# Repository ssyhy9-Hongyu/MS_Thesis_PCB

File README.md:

# MS_Thesis_PCB
PCB version control for current source inverter project

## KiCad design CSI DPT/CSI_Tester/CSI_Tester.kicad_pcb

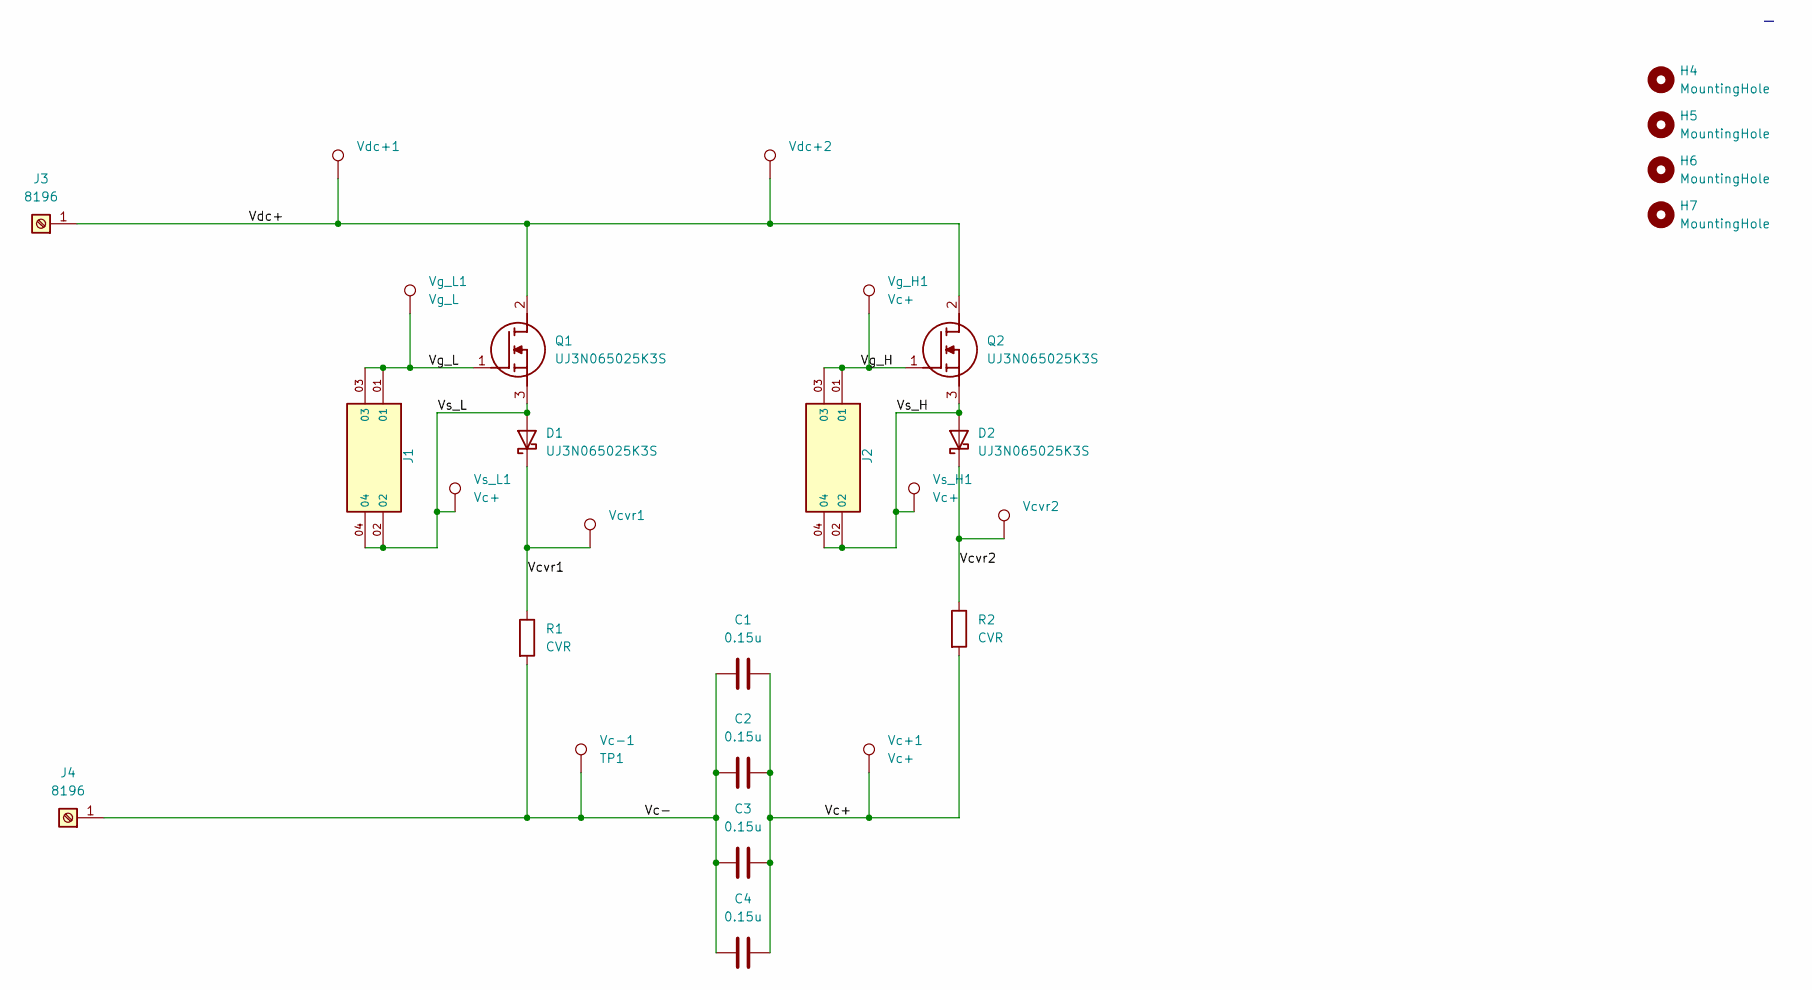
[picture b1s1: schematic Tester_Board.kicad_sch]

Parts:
C1, C2, C3, C4: 0.15u; C_Rect_L26.5mm_W10.5mm_P22.50mm_MKS4
D1, D2: UJ3N065025K3S; TO-247-2_Vertical
H4, H5, H6, H7: MountingHole; MountingHole_4.3mm_M4_DIN965
J1, J2: TSM-102-01-SM-DV; SAMTEC_TSM-102-01-SM-DV
J3, J4: 8196; CONN_8196_KEY
Q1, Q2: UJ3N065025K3S; TO-247-3_Vertical; Manufacturer_Part_Number UJ3N065025K3S
R1, R2: CVR; CVR_SSDN005
Vc+1: Vc+; TestPoint_Pad_D2.0mm
Vc-1: TP1; TestPoint_Pad_D2.0mm
Vcvr1, Vcvr2: TestPoint_Pad_D2.0mm
Vdc+1, Vdc+2: TestPoint_Pad_D2.0mm
Vg_H1: Vc+; TestPoint_Pad_D2.0mm
Vg_L1: Vg_L; TestPoint_Pad_D2.0mm
Vs_H1: Vc+; TestPoint_Pad_D2.0mm
Vs_L1: Vc+; TestPoint_Pad_D2.0mm

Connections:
/Tester_Board/Vc+: C1.2, C2.2, C3.2, C4.2, R2.2, Vc+1.1
/Tester_Board/Vc-: C1.1, C2.1, C3.1, C4.1, J4.1, J4.2, J4.3, J4.4, J4.5, J4.6, R1.2, Vc-1.1
/Tester_Board/Vcvr1: D1.1 (K), R1.1, Vcvr1.1
/Tester_Board/Vcvr2: D2.1 (K), R2.1, Vcvr2.1
/Tester_Board/Vdc+: J3.1, J3.2, J3.3, J3.4, J3.5, J3.6, Q1.2 (D), Q2.2 (D), Vdc+1.1, Vdc+2.1
/Tester_Board/Vg_H: J2.01, J2.03, Q2.1 (G), Vg_H1.1
/Tester_Board/Vg_L: J1.01, J1.03, Q1.1 (G), Vg_L1.1
/Tester_Board/Vs_H: D2.2 (A), J2.02, J2.04, Q2.3 (S), Vs_H1.1
/Tester_Board/Vs_L: D1.2 (A), J1.02, J1.04, Q1.3 (S), Vs_L1.1

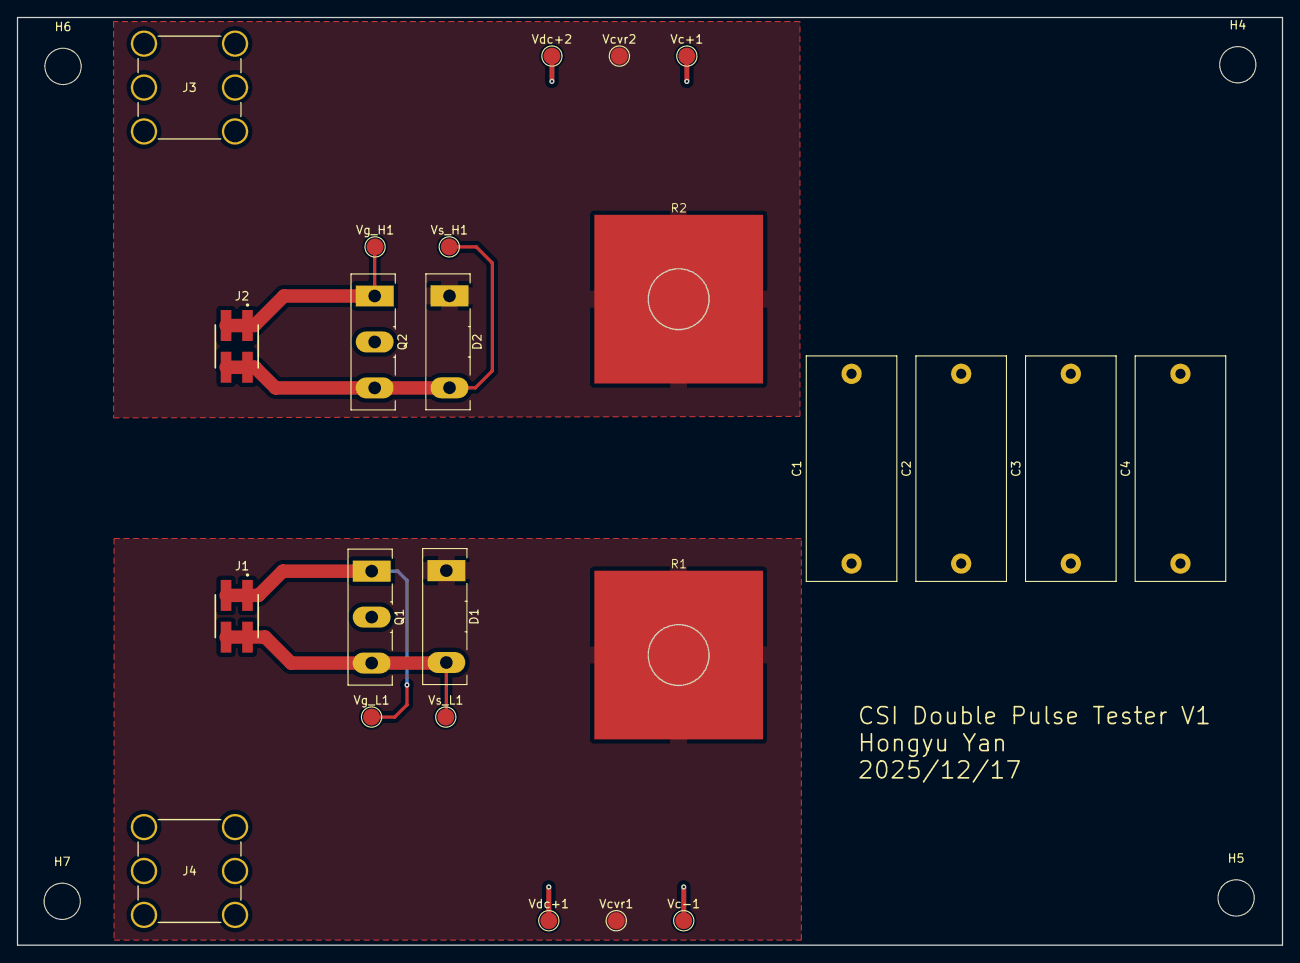
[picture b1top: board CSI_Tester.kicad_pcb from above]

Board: 4 copper layers, 150.0 x 110.0 mm, 28 parts (0 on the bottom side), 9 nets.

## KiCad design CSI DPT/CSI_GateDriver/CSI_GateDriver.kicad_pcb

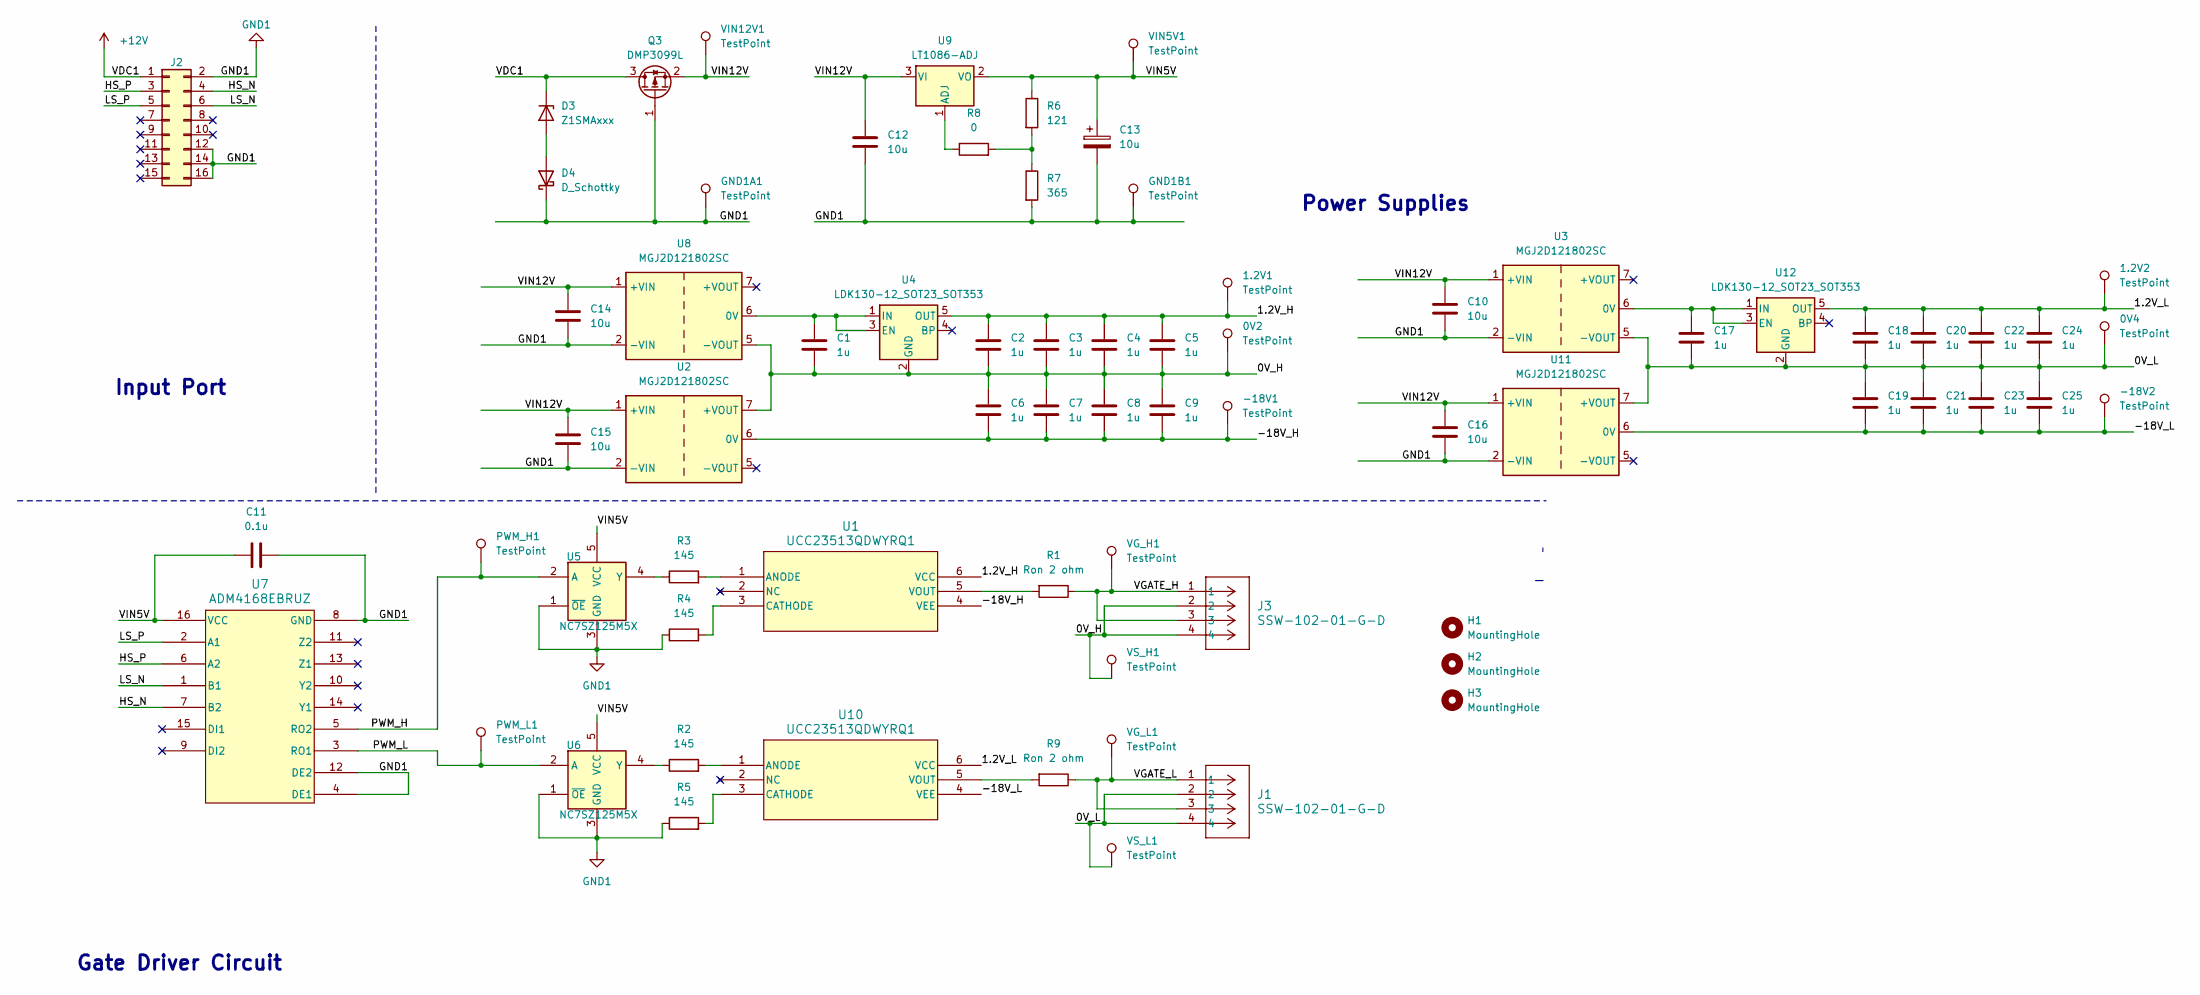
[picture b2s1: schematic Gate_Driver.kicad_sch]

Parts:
0V2, 0V4, 1.2V1, 1.2V2: TestPoint; TestPoint_Pad_D2.0mm
-18V1, -18V2: TestPoint; TestPoint_Pad_D2.0mm
C1, C2, C3, C4, C5, C6, C7, C8, C9, C17, C18, C19, C20, C21, C22, C23, C24, C25: 1u; C_1206_3216Metric
C10, C14, C15, C16: 10u; C_1206_3216Metric
C11: 0.1u; C_1206_3216Metric_Pad1.33x1.80mm_HandSolder
C12: 10u; C_1206_3216Metric_Pad1.33x1.80mm_HandSolder
C13: 10u; TAJB_AVX-M
D3: Z1SMAxxx; D_SMA_Handsoldering
D4: D_Schottky; D_PowerDI-123
GND1A1, GND1B1: TestPoint; TestPoint_Pad_D2.0mm
H1, H2, H3: MountingHole; MountingHole_4.3mm_M4_DIN965
J1, J3: SSW-102-01-G-D; CON4_2X2_TU_SSQ
J2: Conn_02x08_Odd_Even; IDC-Header_2x08_P2.54mm_Vertical
PWM_H1: TestPoint; TestPoint_Pad_D2.0mm
PWM_L1: TestPoint; TestPoint_Pad_D2.0mm
Q3: DMP3099L; SOT-23
R1, R9: Ron 2 ohm; R_1206_3216Metric_Pad1.30x1.75mm_HandSolder
R2, R3, R4, R5: 145; R_1206_3216Metric_Pad1.30x1.75mm_HandSolder
R6: 121; R_1206_3216Metric_Pad1.30x1.75mm_HandSolder
R7: 365; R_1206_3216Metric_Pad1.30x1.75mm_HandSolder
R8: 0; R_1206_3216Metric_Pad1.30x1.75mm_HandSolder
U1, U10: UCC23513QDWYRQ1; SOIC06_SO-6_7P5X4P68_TEX-M
U2, U3, U8, U11: MGJ2D121802SC; Converter_DCDC_Murata_MGJ2DxxxxxxSC_THT
U4, U12: LDK130-12_SOT23_SOT353; SOT-23-5_HandSoldering
U5, U6: NC7SZ125M5X; SOT-23-5_HandSoldering
U7: ADM4168EBRUZ; RU_16_ADI-M
U9: LT1086-ADJ; TO-263-3_TabPin2
VG_H1: TestPoint; TestPoint_Pad_D2.0mm
VG_L1: TestPoint; TestPoint_Pad_D2.0mm
VIN5V1, VIN12V1: TestPoint; TestPoint_Pad_D2.0mm
VS_H1: TestPoint; TestPoint_Pad_D2.0mm
VS_L1: TestPoint; TestPoint_Pad_D2.0mm

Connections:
+12V: D3.1 (K), J2.1, Q3.3 (D)
/Gate_Driver/0V_H: 0V2.1, C1.2, C2.2, C3.2, C4.2, C5.2, C6.1, C7.1, C8.1, C9.1, J3.2, J3.4, U2.7 (+VOUT), U4.2 (GND), U8.5 (-VOUT), VS_H1.1
/Gate_Driver/0V_L: 0V4.1, C17.2, C18.2, C19.1, C20.2, C21.1, C22.2, C23.1, C24.2, C25.1, J1.2, J1.4, U3.5 (-VOUT), U11.7 (+VOUT), U12.2 (GND), VS_L1.1
/Gate_Driver/1.2V_H: 1.2V1.1, C2.1, C3.1, C4.1, C5.1, U1.6 (VCC), U4.5 (OUT)
/Gate_Driver/1.2V_L: 1.2V2.1, C18.1, C20.1, C22.1, C24.1, U10.6 (VCC), U12.5 (OUT)
/Gate_Driver/-18V_H: -18V1.1, C6.2, C7.2, C8.2, C9.2, U1.4 (VEE), U2.6 (0V)
/Gate_Driver/-18V_L: -18V2.1, C19.2, C21.2, C23.2, C25.2, U10.4 (VEE), U11.6 (0V)
/Gate_Driver/HS_N: J2.4, U7.7 (B2)
/Gate_Driver/HS_P: J2.3, U7.6 (A2)
/Gate_Driver/LS_N: J2.6, U7.1 (B1)
/Gate_Driver/LS_P: J2.5, U7.2 (A1)
/Gate_Driver/PWM_H: PWM_H1.1, U5.2 (A), U7.5 (RO2)
/Gate_Driver/PWM_L: PWM_L1.1, U6.2 (A), U7.3 (RO1)
/Gate_Driver/VGATE_H: J3.1, J3.3, R1.1, VG_H1.1
/Gate_Driver/VGATE_L: J1.1, J1.3, R9.1, VG_L1.1
/Gate_Driver/VIN5V: C11.1, C13.1, R6.1, U5.5 (VCC), U6.5 (VCC), U7.16 (VCC), U9.2 (VO), VIN5V1.1
/Gate_Driver/VIN12V: C10.1, C12.1, C14.1, C15.1, C16.1, Q3.2 (S), U2.1 (+VIN), U3.1 (+VIN), U8.1 (+VIN), U9.3 (VI), U11.1 (+VIN), VIN12V1.1
GND1: C10.2, C11.2, C12.2, C13.2, C14.2, C15.2, C16.2, D4.1 (K), GND1A1.1, GND1B1.1, J2.2, J2.12, J2.14, J2.16, Q3.1 (G), R4.1, R5.1, R7.2, U2.2 (-VIN), U3.2 (-VIN), U5.1 (~OE), U5.3 (GND), U6.1 (~OE), U6.3 (GND), U7.4 (DE1), U7.8 (GND), U7.12 (DE2), U8.2 (-VIN), U11.2 (-VIN)
unnamed: D3.2 (A), D4.2 (A)
unnamed: R6.2, R7.1, R8.2
unnamed: R3.2, U1.1 (ANODE)
unnamed: R4.2, U1.3 (CATHODE)
unnamed: R1.2, U1.5 (VOUT)
unnamed: C1.1, U4.1 (IN), U4.3 (EN), U8.6 (0V)
unnamed: R3.1, U5.4 (Y)
unnamed: R2.1, U6.4 (Y)
unnamed: R8.1, U9.1 (ADJ)
unnamed: R2.2, U10.1 (ANODE)
unnamed: R5.2, U10.3 (CATHODE)
unnamed: R9.2, U10.5 (VOUT)
unnamed: C17.1, U3.6 (0V), U12.1 (IN), U12.3 (EN)

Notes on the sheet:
Gate Driver Circuit
Power Supplies
Input Port

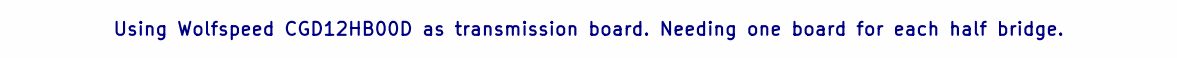
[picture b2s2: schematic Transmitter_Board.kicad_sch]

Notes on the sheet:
Using Wolfspeed CGD12HB00D as transmission board. Needing one board for each half bridge.

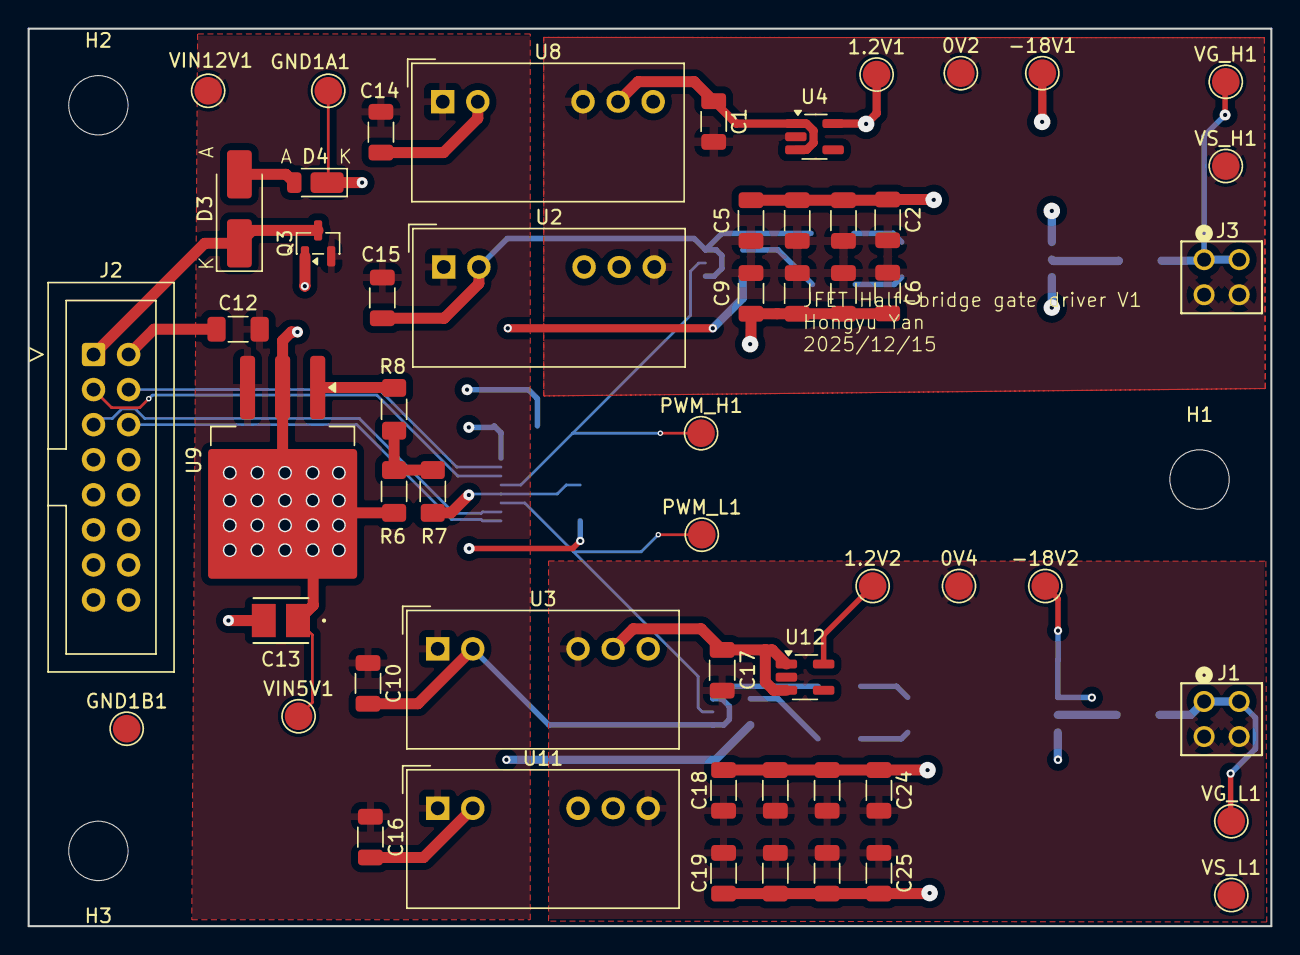
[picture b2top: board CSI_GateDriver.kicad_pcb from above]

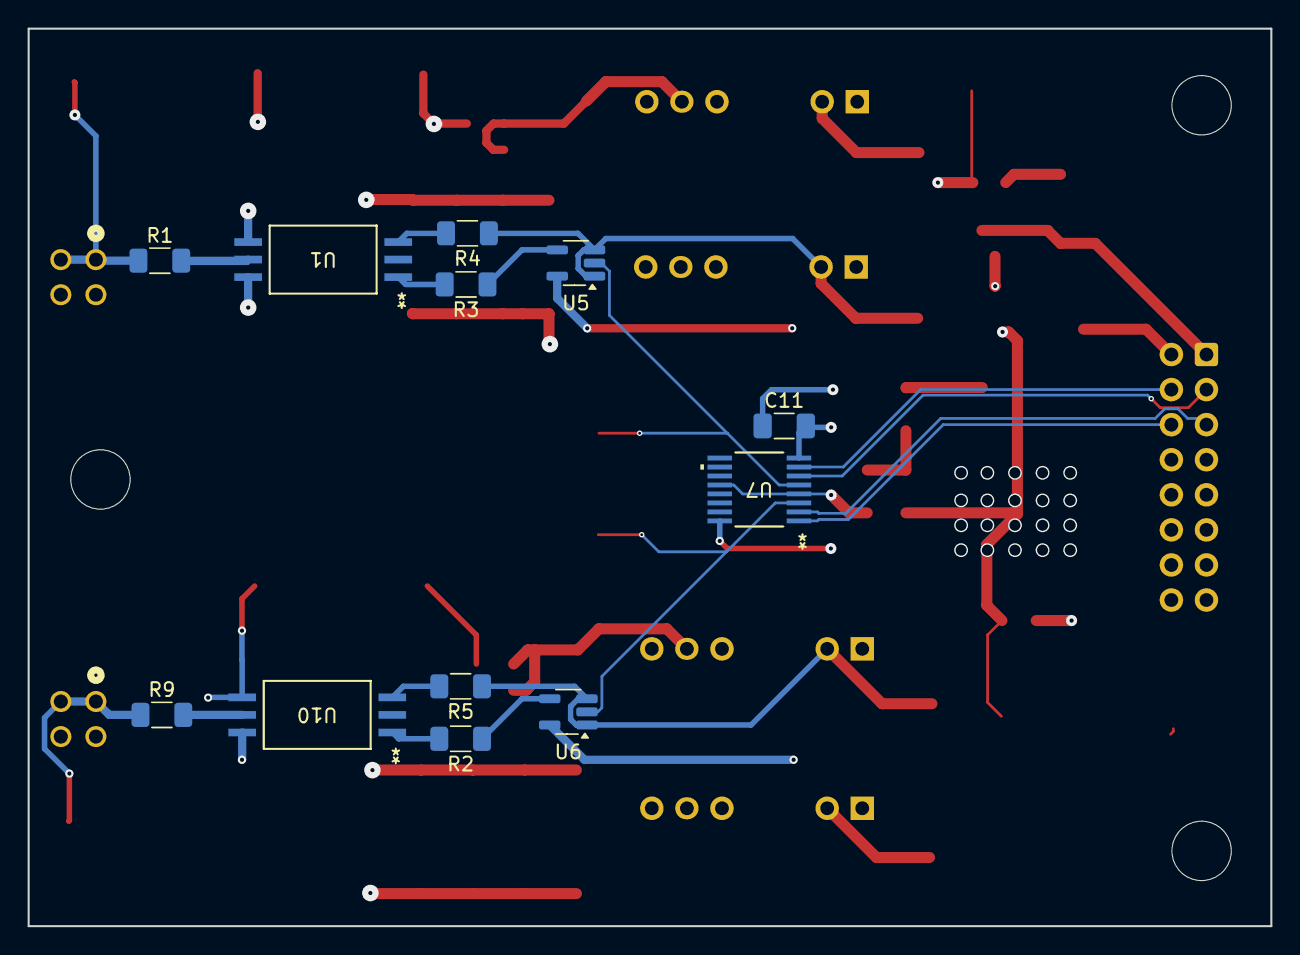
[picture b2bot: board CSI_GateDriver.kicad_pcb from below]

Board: 4 copper layers, 90.0 x 65.0 mm, 71 parts (12 on the bottom side), 31 nets.

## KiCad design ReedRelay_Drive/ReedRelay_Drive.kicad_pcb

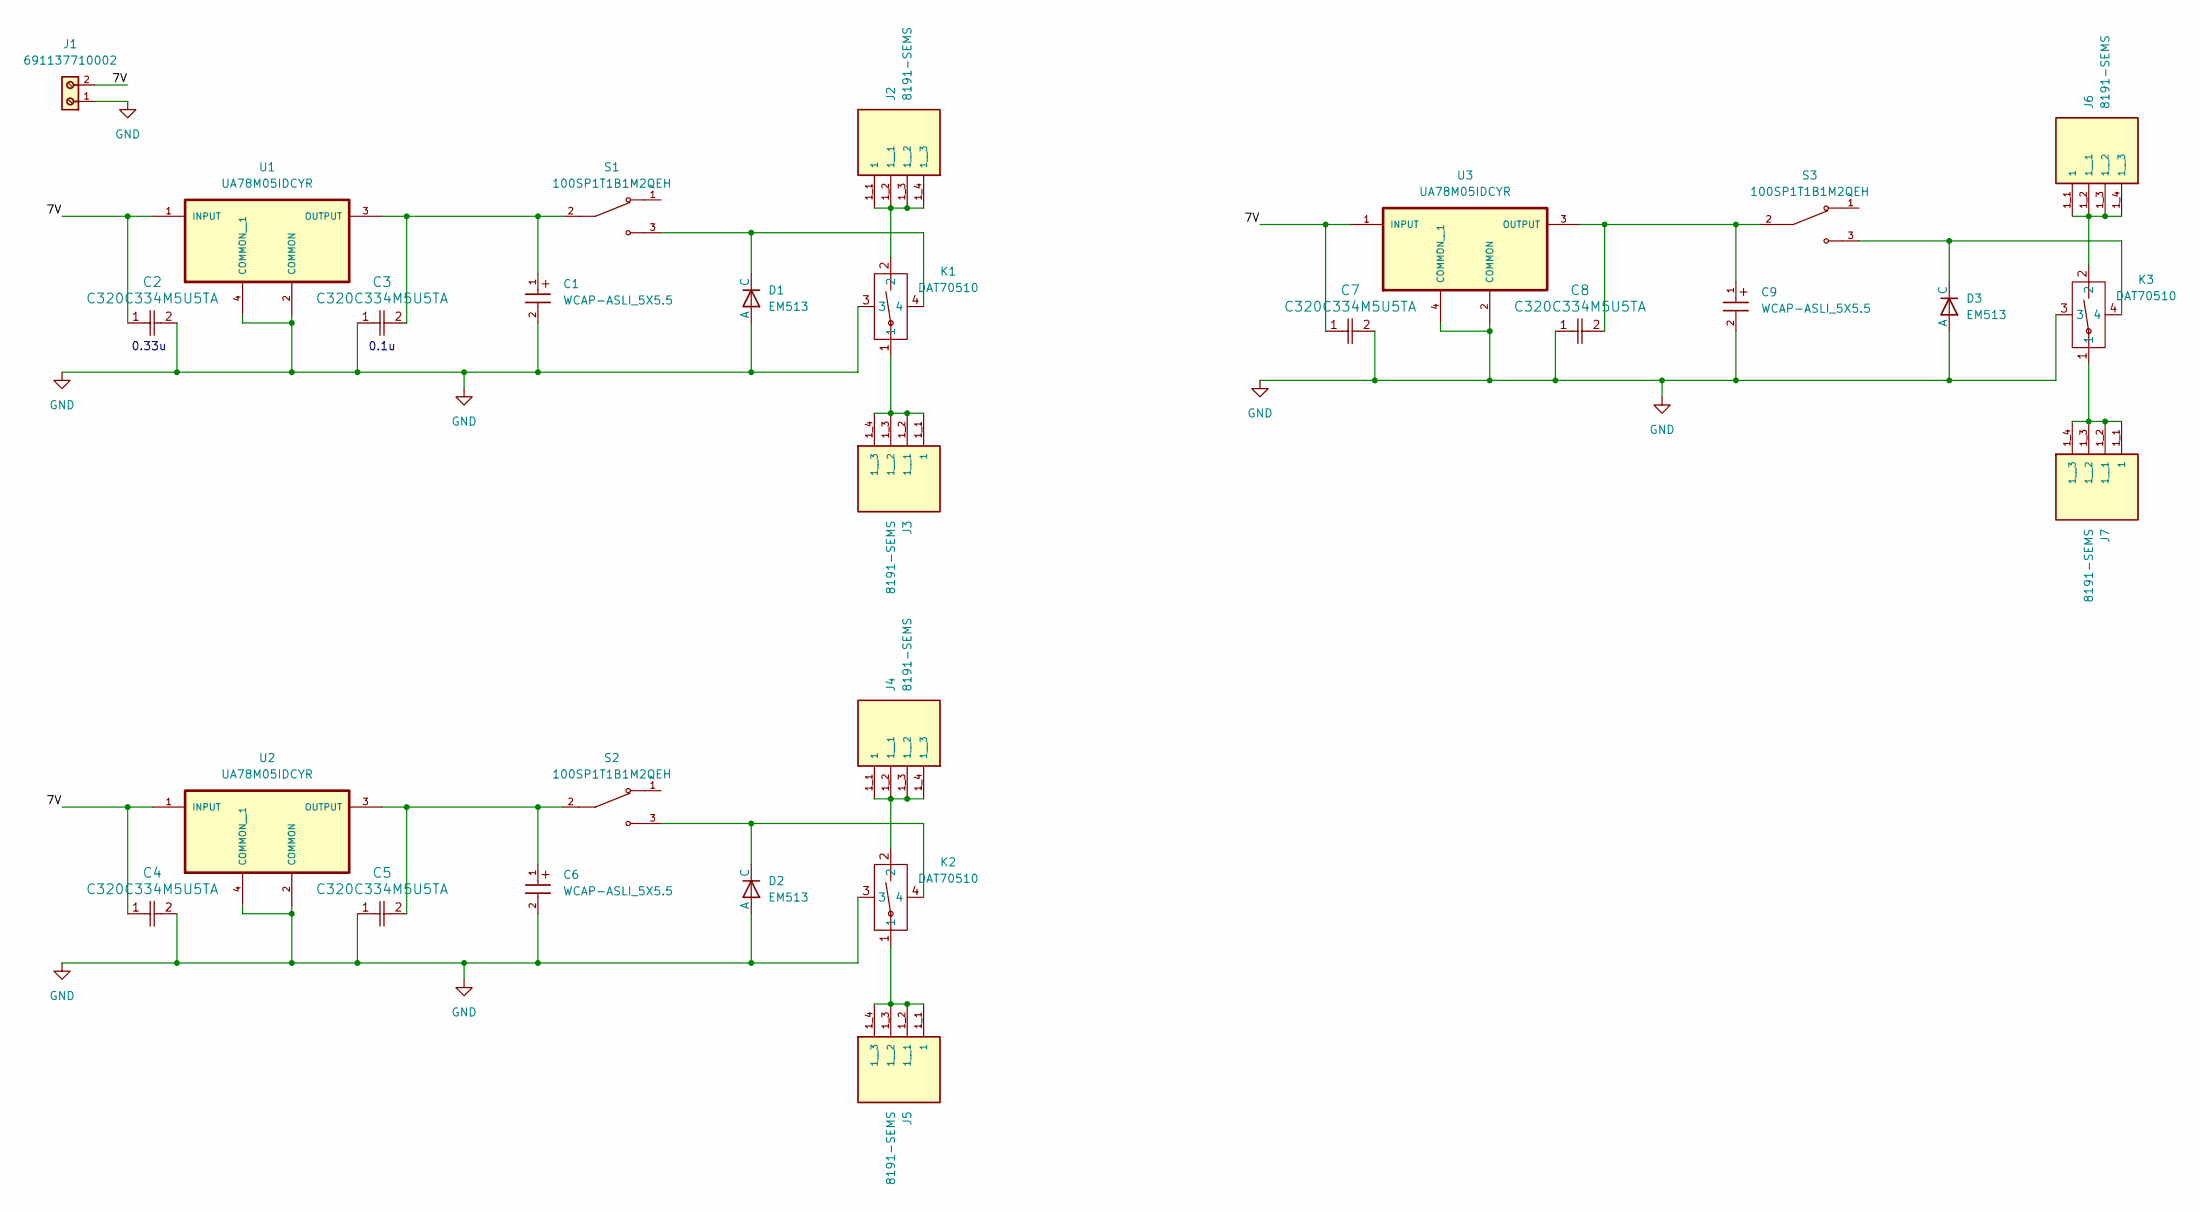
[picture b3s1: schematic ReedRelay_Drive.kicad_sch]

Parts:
C1, C6, C9: WCAP-ASLI_5X5.5; 47u_cap_865080342006
C2, C3, C4, C5, C7, C8: C320C334M5U5TA; CAP_C320_KEM
D1, D2, D3: EM513; P1_DO-41
J1: 691137710002
J2, J3, J4, J5, J6, J7: 8191-SEMS; KEYSTONE_8191-SEMS; PARTREV G
K1, K2, K3: DAT70510
S1, S2, S3: 100SP1T1B1M2QEH; SW_100SP1T1B1M2QEH; PARTREV B; DigiKey_Part_Number EG2352-ND
U1, U2, U3: UA78M05IDCYR; SOT230P700X180-4N

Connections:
/7V: C2.1, C4.1, C7.1, J1.2, U1.1 (INPUT), U2.1 (INPUT), U3.1 (INPUT)
GND: C1.2, C2.2, C3.1, C4.2, C5.1, C6.2, C7.2, C8.1, C9.2, D1.1 (A), D2.1 (A), D3.1 (A), J1.1, K1.3, K2.3, K3.3, U1.2 (COMMON), U1.4 (COMMON__1), U2.2 (COMMON), U2.4 (COMMON__1), U3.2 (COMMON), U3.4 (COMMON__1)
unnamed: D1.2 (C), K1.4, S1.3
unnamed: D2.2 (C), K2.4, S2.3
unnamed: D3.2 (C), K3.4, S3.3
unnamed: J2.1_1 (1), J2.1_2 (1__1), J2.1_3 (1__2), J2.1_4 (1__3), K1.2
unnamed: J3.1_1 (1), J3.1_2 (1__1), J3.1_3 (1__2), J3.1_4 (1__3), K1.1
unnamed: J4.1_1 (1), J4.1_2 (1__1), J4.1_3 (1__2), J4.1_4 (1__3), K2.2
unnamed: J5.1_1 (1), J5.1_2 (1__1), J5.1_3 (1__2), J5.1_4 (1__3), K2.1
unnamed: J6.1_1 (1), J6.1_2 (1__1), J6.1_3 (1__2), J6.1_4 (1__3), K3.2
unnamed: J7.1_1 (1), J7.1_2 (1__1), J7.1_3 (1__2), J7.1_4 (1__3), K3.1
unnamed: C1.1, C3.2, S1.2, U1.3 (OUTPUT)
unnamed: C5.2, C6.1, S2.2, U2.3 (OUTPUT)
unnamed: C8.2, C9.1, S3.2, U3.3 (OUTPUT)

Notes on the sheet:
0.1u
0.33u

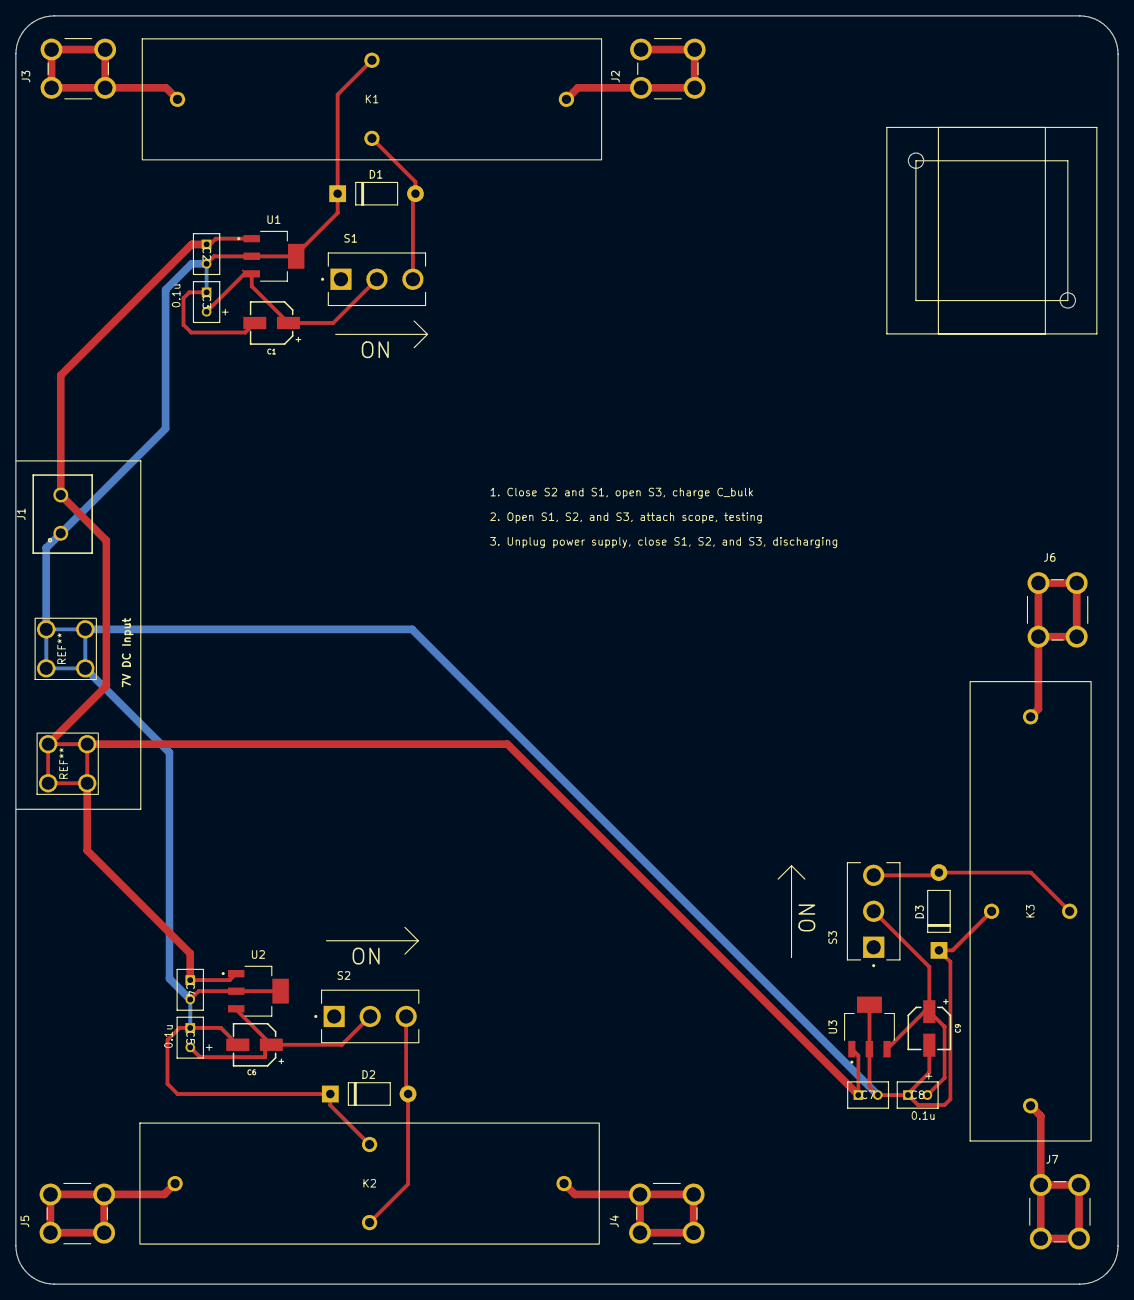
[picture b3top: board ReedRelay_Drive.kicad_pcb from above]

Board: 2 copper layers, 144.0 x 165.7 mm, 28 parts (0 on the bottom side), 14 nets.

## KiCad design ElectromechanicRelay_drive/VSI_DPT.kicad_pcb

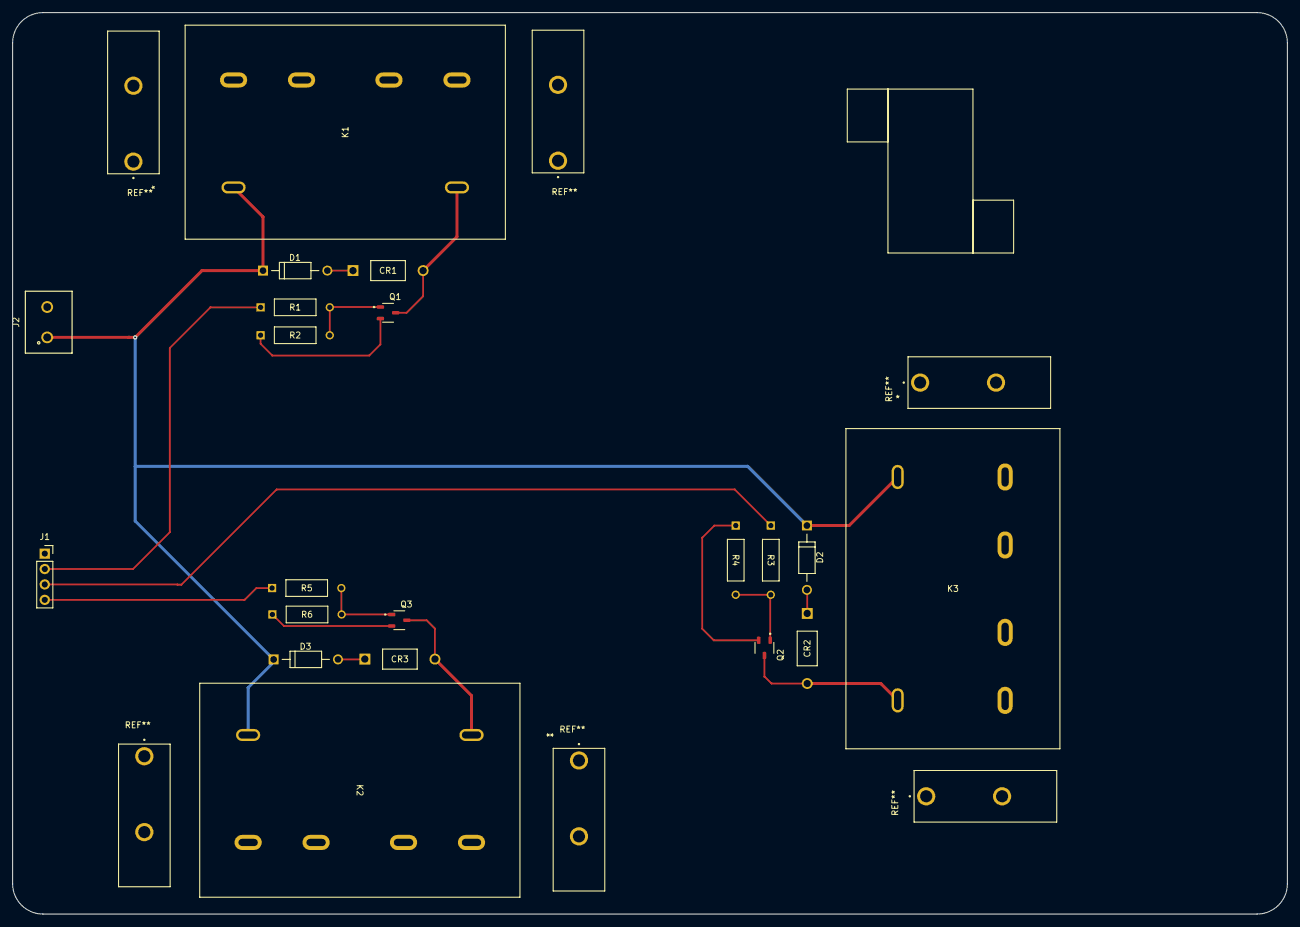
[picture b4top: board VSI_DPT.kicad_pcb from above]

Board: 2 copper layers, 210.0 x 148.5 mm, 20 parts (0 on the bottom side), 17 nets.

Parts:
CR1, CR2, CR3: 1N4751A; DIODE_AFL-W2Y1.8D_MOT
D1, D2, D3: 1N4007; DIOAD1060W80L520D270
J1: Conn_01x04_Socket; PinSocket_1x04_P2.54mm_Vertical
J2: 691137710002
K1, K2, K3: G7L-2A-X-SI DC24; RELAY_G7L-2A-X_OMR
Q1, Q2, Q3: AO3400A; SOT95P280X125-3N
R1, R3, R5: YR1B1K0CC
R2, R4, R6: YR1B10KCC

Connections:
+24V: D1.C, D2.C, D3.C, J2.1, K1.1, K2.0, K3.1
/lower_ctl: J1.4, R5.1
/middle_ctl: J1.3, R3.1
/upper_ctl: J1.2, R1.1
GND: J1.1, J2.2, Q1.2, Q2.2, Q3.2, R2.1, R4.1, R6.1
unnamed: CR1.1 (A), K1.0, Q1.3
unnamed: CR1.2 (K), D1.A
unnamed: CR2.1 (A), K3.0, Q2.3
unnamed: CR2.2 (K), D2.A
unnamed: CR3.1 (A), K2.1, Q3.3
unnamed: CR3.2 (K), D3.A
unnamed: Q1.1, R1.2, R2.2
unnamed: Q2.1, R3.2, R4.2
unnamed: Q3.1, R5.2, R6.2
Relay1_M: K1.4, K1.6
Relay2_M: K3.4, K3.6
Relay3_M: K2.4, K2.6

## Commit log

2025-11-16 Initial repo
    1. Reed relay drivers for VSI DPT
    2. Electromechanical relay drivers for VSI DPT
    3. Double pulse tester from Wolfspeed
    4. Gate driver design for JFET using opto transmitter (in CSI DPT folder)
2025-11-18 Nov.17 Update
    Changed from opto PWM transmission to differential transmission. With added test point.
2025-11-18 Nov.18 Update 1
    temporary save
2025-11-18 Nov.18 Update 1
    temp
2025-11-18 Nov.18 Update 2
    1. Finish PCB layout
2025-12-01 test commit
2025-12-04 Gate Driver Complete
    1. Competed half bridge gate driver
2025-12-04 Picking up
    1. Tidy up the project folders, one project split into two projects (gate driver + tester)
    2. Gate driver PCB half way done
2025-12-15 Completed gate driver V1
    1. finished the PCB layout of gate driver V1, waiting for feedback
2025-12-17 CSI Tester V1 Completed
2026-01-05 Size down the boards
